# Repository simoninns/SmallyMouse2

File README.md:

## Synopsis

SmallyMouse2 is the AT90USB1287 firmware source code and KiCAD schematic/PCB design for the SmallyMouse2 project.

## Motivation

SmallyMouse2 is a project that creates a USB mouse adaptor for retro computers that use quadrature mouse input including the Acorn BBC Micro, Acorn Master series, Commodore Amiga, Atari ST, busmouse compatible computers and many more.  SmallyMouse2 provides both a generic mouse output header (for attaching mouse to retro computer cables) and an IDC connector suitable for use with Acorn 8-bit user-ports.  SmallyMouse2 also features a configurable quadrature rate limiter that prevents VIA overrun when in use with slower 8-bit machines.

SmallyMouse2 supports both JTAG and USB bootloader programming.  The AT90USB1287 is pre-programmed by Atmel with the (FLIP) DFU bootloader; this bootloader is recognised by Atmel Studio as a programming device and can be used to flash the firmware to the board.

## Installation

Note: This is an Atmel Studio 7 project that can be loaded and compiled by the IDE

Please see http://www.waitingforfriday.com/?p=827 for detailed documentation about SmallyMouse2

## Author

SmallyMouse2 is written and maintained by Simon Inns.

## License (Software)

    SmallyMouse2 is free software: you can redistribute it and/or modify
    it under the terms of the GNU General Public License as published by
    the Free Software Foundation, either version 3 of the License, or
    (at your option) any later version.

    SmallyMouse2 is distributed in the hope that it will be useful,
    but WITHOUT ANY WARRANTY; without even the implied warranty of
    MERCHANTABILITY or FITNESS FOR A PARTICULAR PURPOSE.  See the
    GNU General Public License for more details.

    You should have received a copy of the GNU General Public License
    along with SmallyMouse2. If not, see <http://www.gnu.org/licenses/>.

## License (Hardware)

Both the schematic and the PCB design of SmallyMouse2 (i.e. the KiCAD project and files) are covered by a Creative Commons license; as with the software you are welcome (and encouraged!) to extend, re-spin and otherwise use and modify the design as allowed by the license.  However; under the terms of the Attribution-ShareAlike 4.0 International (CC BY-SA 4.0) license you are required to release your design (or redesign) under the same license.  For details of the licensing requirements please see <https://creativecommons.org/licenses/by-sa/4.0/>

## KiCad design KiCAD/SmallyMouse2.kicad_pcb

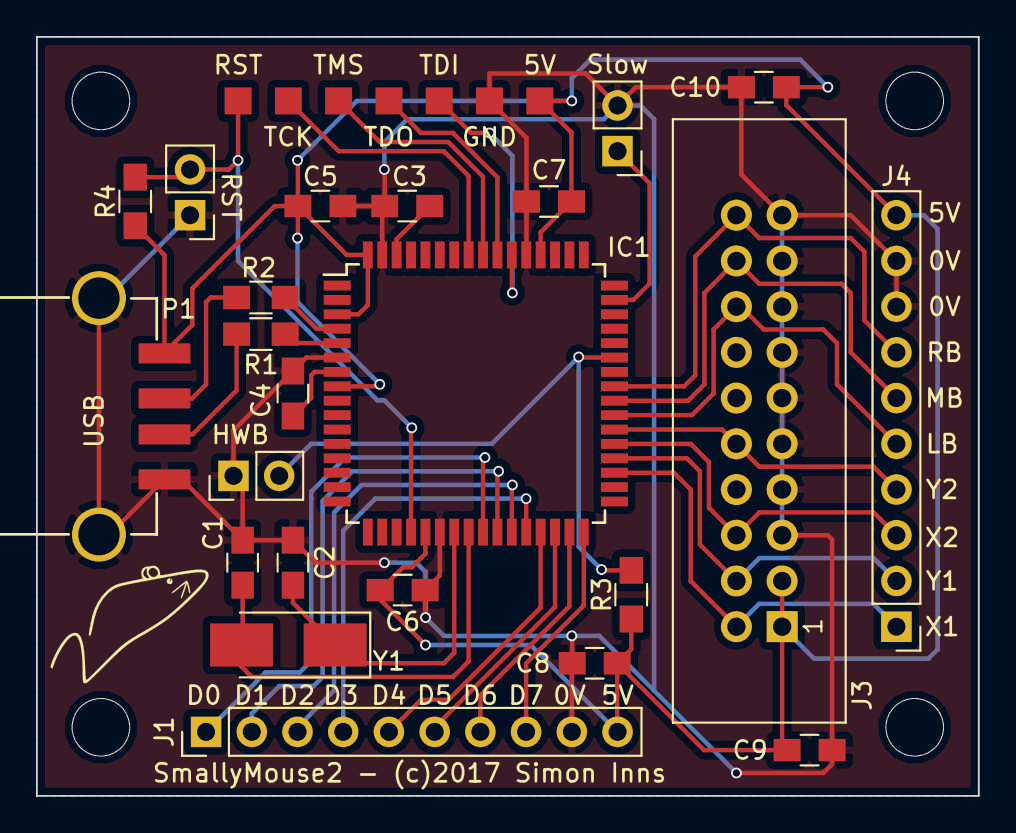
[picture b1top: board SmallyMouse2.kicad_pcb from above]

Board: 2 copper layers, 52.3 x 42.2 mm, 34 parts (0 on the bottom side), 32 nets.

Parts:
5V: +5V; Measurement_Point_Square-SMD-Pad_Small
C1, C2: 22pF; C_0805_HandSoldering
C3, C5, C6, C7, C8, C9, C10: 100nF; C_0805_HandSoldering
C4: 1uF; C_0805_HandSoldering
GND: GND; Measurement_Point_Square-SMD-Pad_Small
IC1: AT90USB1287; TQFP-64_14x14mm_Pitch0.8mm
J1: Exp Header; Pin_Header_Straight_1x10_Pitch2.54mm
J2: Slow/Fast; Pin_Header_Straight_1x02_Pitch2.54mm
J3: BBC_UP_02X10; IDC_Header_Straight_20pins
J4: Universal output; Pin_Header_Straight_1x10_Pitch2.54mm
J5: Bootloader; Pin_Header_Straight_1x02_Pitch2.54mm
J6: Reset; Pin_Header_Straight_1x02_Pitch2.54mm
MK1, MK2, MK3, MK4: Mounting_Hole; MountingHole_3.2mm_M3_ISO14580
P1: USB_A; Amphenol_87583-2010BLF
R1, R2: 22R; R_0805_HandSoldering
R3, R4: 10K; R_0805_HandSoldering
RST: ~RESET; Measurement_Point_Square-SMD-Pad_Small
TCK: TCK; Measurement_Point_Square-SMD-Pad_Small
TDI: TDI; Measurement_Point_Square-SMD-Pad_Small
TDO: TDO; Measurement_Point_Square-SMD-Pad_Small
TMS: TMS; Measurement_Point_Square-SMD-Pad_Small
Y1: 16 MHz Crystal; Crystal_SMD_5032-2pin_5.0x3.2mm_HandSoldering

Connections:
+5V: 5V.1, C5.2, C6.2, C7.2, C8.2, C9.2, C10.2, IC1.3, IC1.8, IC1.21, IC1.52, IC1.64, J1.10, J3.1, J3.3, J4.10, P1.1, R3.2, R4.2
GND: C1.2, C2.2, C3.2, C4.2, C5.1, C6.1, C7.1, C8.1, C9.1, C10.1, GND.1, IC1.6, IC1.22, IC1.53, IC1.63, J1.9, J2.2, J3.5, J3.7, J3.9, J3.11, J3.13, J3.15, J3.17, J3.19, J4.8, J4.9, J5.1, J6.1, P1.4, P1.5
L_Button: IC1.39, J3.16, J4.5
M_Button: IC1.40, J3.18, J4.6
unnamed: C1.1, IC1.24, Y1.2
unnamed: C2.1, IC1.23, Y1.1
unnamed: C3.1, IC1.62
unnamed: C4.1, IC1.7
unnamed: IC1.4, R2.1
unnamed: IC1.5, R1.1
unnamed: IC1.20, J6.2, R4.1, RST.1
unnamed: IC1.25, J1.1
unnamed: IC1.26, J1.2
unnamed: IC1.27, J1.3
unnamed: IC1.28, J1.4
unnamed: IC1.29, J1.5
unnamed: IC1.30, J1.6
unnamed: IC1.31, J1.7
unnamed: IC1.32, J1.8
unnamed: IC1.43, J5.2, R3.1
unnamed: IC1.47, J2.1
unnamed: IC1.54, TDI.1
unnamed: IC1.55, TDO.1
unnamed: IC1.56, TMS.1
unnamed: IC1.57, TCK.1
unnamed: P1.2, R2.2
unnamed: P1.3, R1.2
R_Button: IC1.41, J3.20, J4.7
X1: IC1.35, J3.2, J4.1
X2: IC1.37, J3.6, J4.3
Y1: IC1.36, J3.4, J4.2
Y2: IC1.38, J3.10, J4.4

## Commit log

2017-05-25 :octocat: Added .gitattributes
2017-05-25 Initial push of firmware
2017-05-25 Added KiCAD schematic and PCB files
    KiCAD schematic and PCB files include gerber output for board
    fabrication
2017-05-27 Fixes to KiCAD project files and addition PDF of schematic
2017-05-27 Updated PCB board files with title and licensing information
2017-05-27 Updated readme with KiCAD project license details
2017-05-27 Updated readme summary
2017-05-27 Added project logo
    Project logo in PNG and Adobe Illustrator format
2017-05-27 Added logotype license
2017-05-27 Corrected readme text format
2017-05-27 Update to readme with new project URL
2017-05-28 Major code rewrite
    Improved code overall for smoother quadrature output and better
    performance. Lots of fixes to the code in terms of making it easier to
    understand and easier to configure.
2017-05-30 Rewrite of quadrature output routines
    Rewrite of quadrature output routines to make them smoother, more
    analogue in nature and also more accurate. Max hertz output is now
    correctly limited and the buffer limit and rate limit features have been
    improved
2017-05-30 Corrections to ratelimit calculations
    Corrections to ratelimit calculations to ensure correct timing according
    the the rate limit hertz configuration setting. Previous version had a
    bug in the calculations. Also change quadrature output to default to 0
    when idle. This is to prevent SmallyMouse2 from supplying power to the
    host (when SmallyMouse is self-powered and the host is off).
2017-05-31 Minor corrections to comments
2017-05-31 Fixes for issues #1 and #2
    Fixes for issues #1 and #2. Inverted mouse buttons initialisation state
    and removed 'quadrature output reset' from interrupt code
2020-02-08 Updated headers and added notice on hardware licensing for issue #9
2020-02-08 Lowered rate limit and added DPI divider jumper on E7/0V of the expansion header - issue #7
2020-02-08 Changed mouse button GPIOs to support open-drain - fix for issue #8
2020-02-08 Fix for issue #10 - caused by lag in changing quadrature phase when reversing direction
2020-02-08 Added comments around the phase reset to make it clearer
2020-07-30 Bug fix for issue #12
    Solves issue with pointer motion when right button is held down
2020-07-30 Fix for issue #10
    Changed the order in which new mouse motion is output; code now change phase first then outputs the phase to the IO
2020-08-04 Add Makefile for avr-gcc.
2020-11-14 Fixes according to issue #15
2020-11-28 Fix for issue #13
    Added version number to serial output
2020-11-28 Small bug fix from testing
2021-04-26 This proposed change stops the inverse mouse acceleration effect under DPI dividing.
    Instead of placing a floor of one movement unit output for any movement units input, a pair of static locals track skipped units allowing the divisor to also work where input movementUnits < DPI_DIVI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
2023-12-07 Updated header files and improved Makefile including JTAG programming via Atmel-ICE
2023-12-07 Improved makefile and included example CFLAGS for buggy USB mice. Changed debug console to include github URL.

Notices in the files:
KiCAD/SmallyMouse2.kicad_pcb:
(c)2017 Simon Inns
License: Attribution-ShareAlike 4.0 International (CC BY-SA 4.0)
SmallyMouse2 - (c)2017 Simon Inns
